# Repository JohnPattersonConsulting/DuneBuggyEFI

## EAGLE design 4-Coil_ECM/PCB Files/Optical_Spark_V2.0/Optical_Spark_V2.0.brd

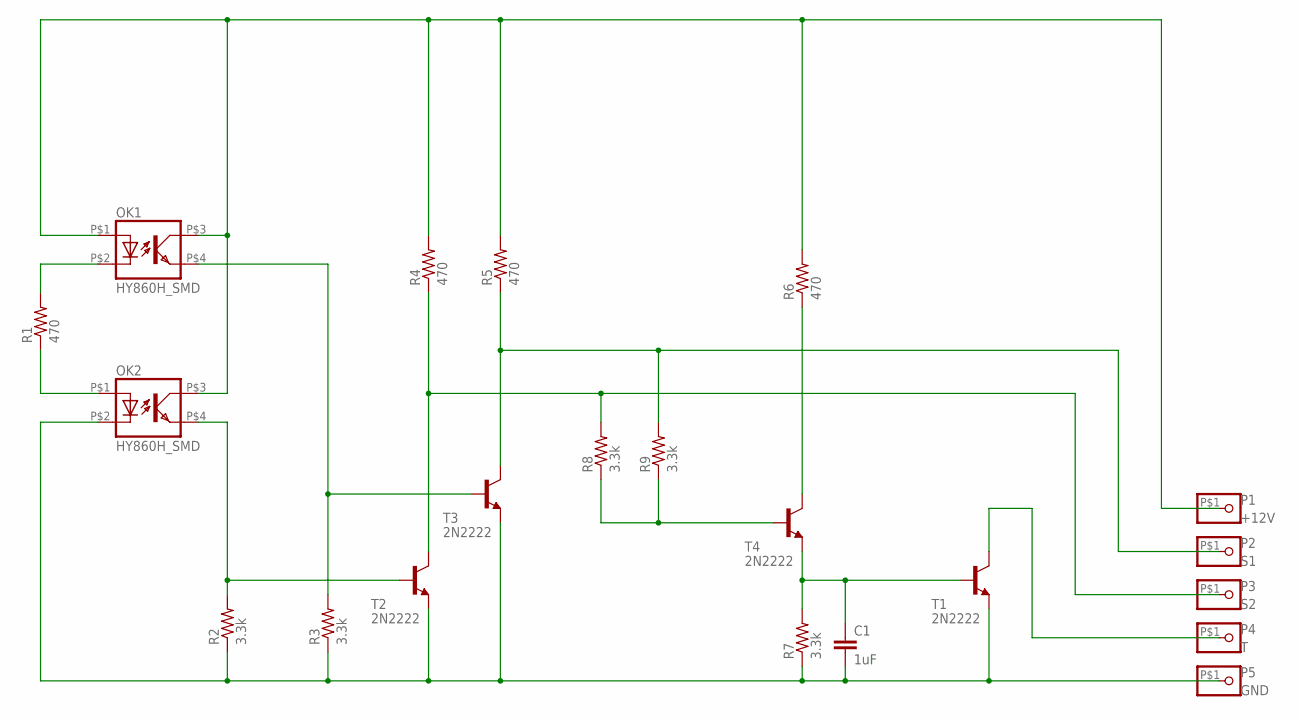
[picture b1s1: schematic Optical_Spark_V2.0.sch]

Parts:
C1: 1uF; SMALLCAP_THT_SMD
OK1, OK2: HY860H_SMD
P1: +12V; PAD
P2: S1; PAD
P3: S2; PAD
P4: T; PAD
P5: GND; PAD
R1, R4, R5, R6: 470; 0.25W_THT_SMD
R2, R3, R7, R8, R9: 3.3k; 0.25W_THT_SMD_SMALL
T1, T2, T3, T4: 2N2222; NPN_THT_SMD_EBC

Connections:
unnamed: OK1.P$2 (C), R1.P$2 (2)
unnamed: OK2.P$1 (A), R1.P$1 (1)
unnamed: C1.P$2 (2), OK2.P$2 (C), P5.P$1, R2.P$1 (1), R3.P$1 (1), R7.P$1 (1), T1.P$1 (E), T2.P$1 (E), T3.P$1 (E)
unnamed: OK1.P$1 (A), OK1.P$3 (COL), OK2.P$3 (COL), P1.P$1, R4.P$2 (2), R5.P$2 (2), R6.P$2 (2)
unnamed: C1.P$1 (1), R7.P$2 (2), T1.P$2 (B), T4.P$1 (E)
unnamed: OK2.P$4 (EMIT), R2.P$2 (2), T2.P$2 (B)
unnamed: OK1.P$4 (EMIT), R3.P$2 (2), T3.P$2 (B)
unnamed: P2.P$1, R5.P$1 (1), R9.P$2 (2), T3.P$3 (C)
unnamed: P3.P$1, R4.P$1 (1), R8.P$2 (2), T2.P$3 (C)
unnamed: R6.P$1 (1), T4.P$3 (C)
unnamed: P4.P$1, T1.P$3 (C)
unnamed: R8.P$1 (1), R9.P$1 (1), T4.P$2 (B)

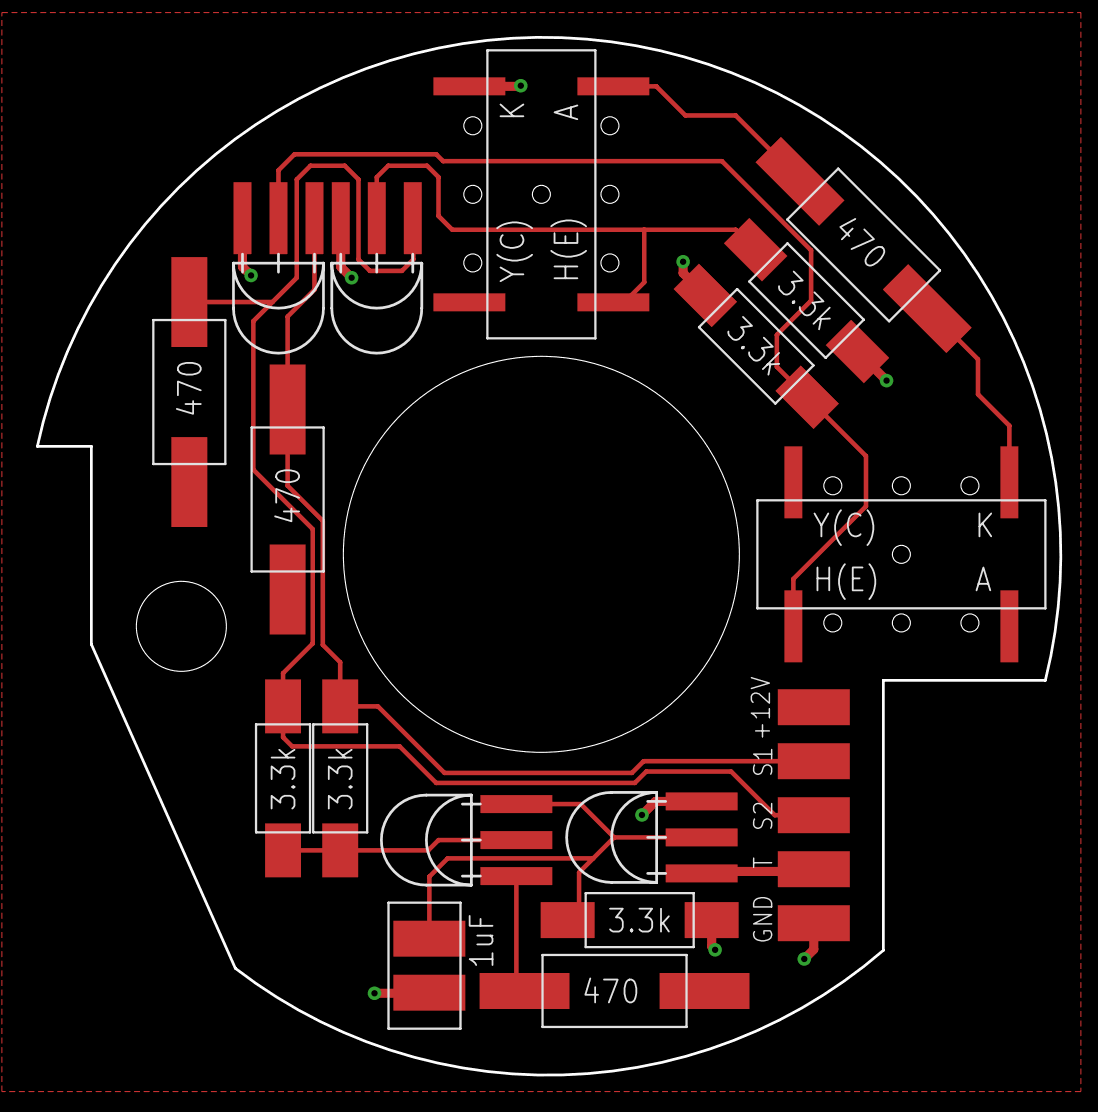
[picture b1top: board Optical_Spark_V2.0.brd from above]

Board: 2 copper layers, 56.9 x 57.6 mm, 21 parts (0 on the bottom side), 12 nets.

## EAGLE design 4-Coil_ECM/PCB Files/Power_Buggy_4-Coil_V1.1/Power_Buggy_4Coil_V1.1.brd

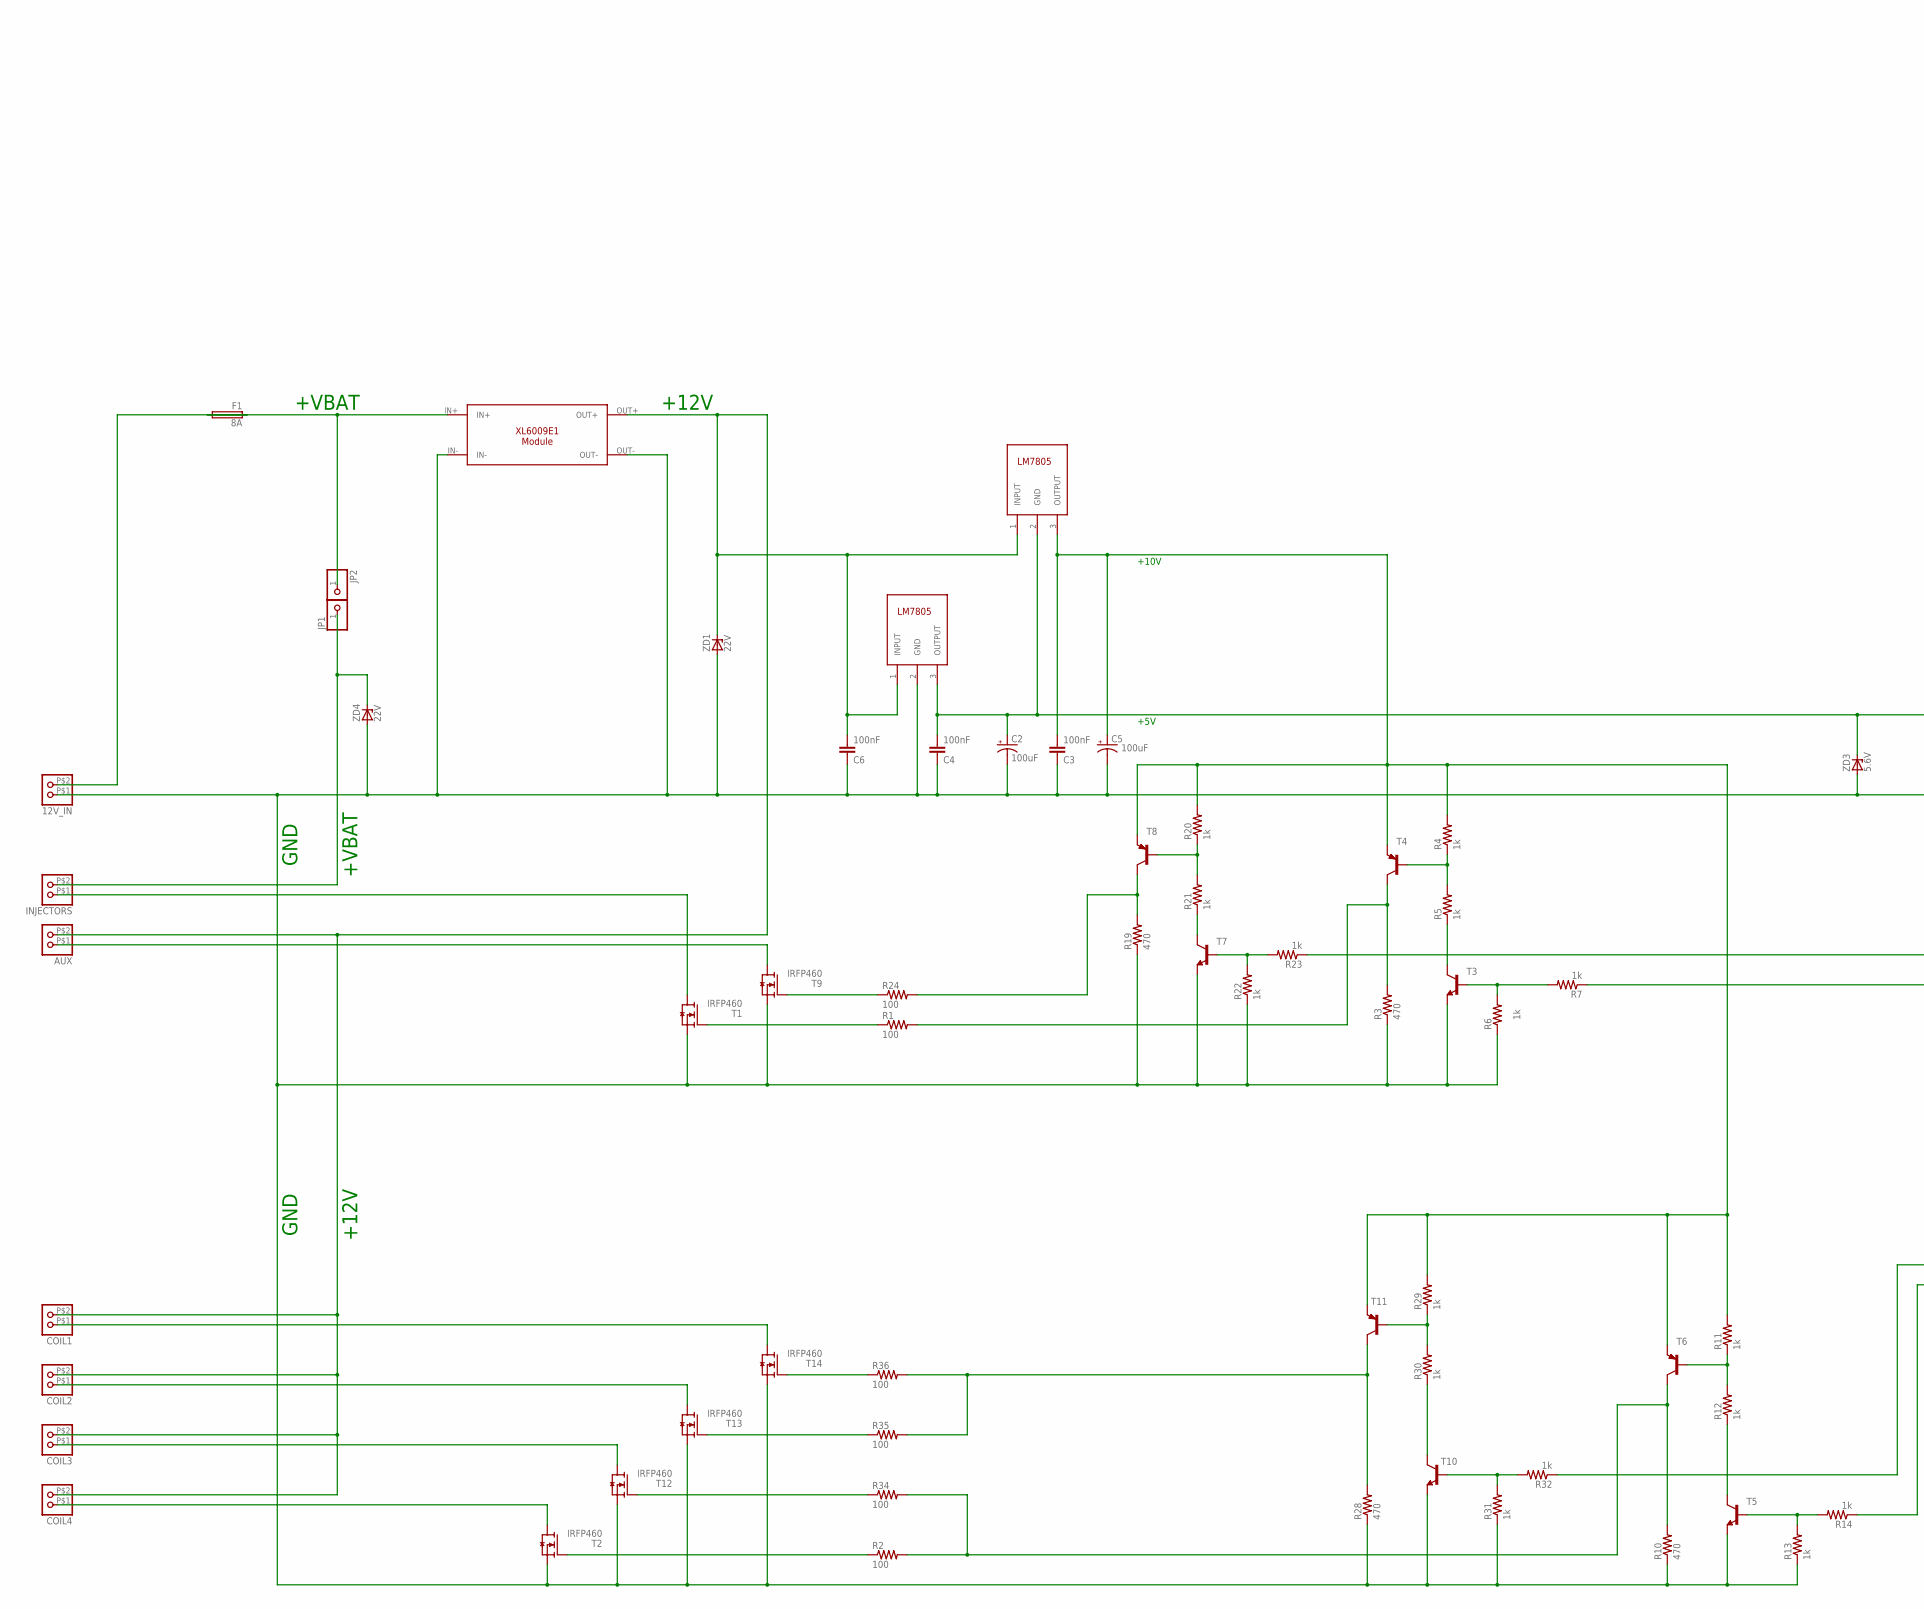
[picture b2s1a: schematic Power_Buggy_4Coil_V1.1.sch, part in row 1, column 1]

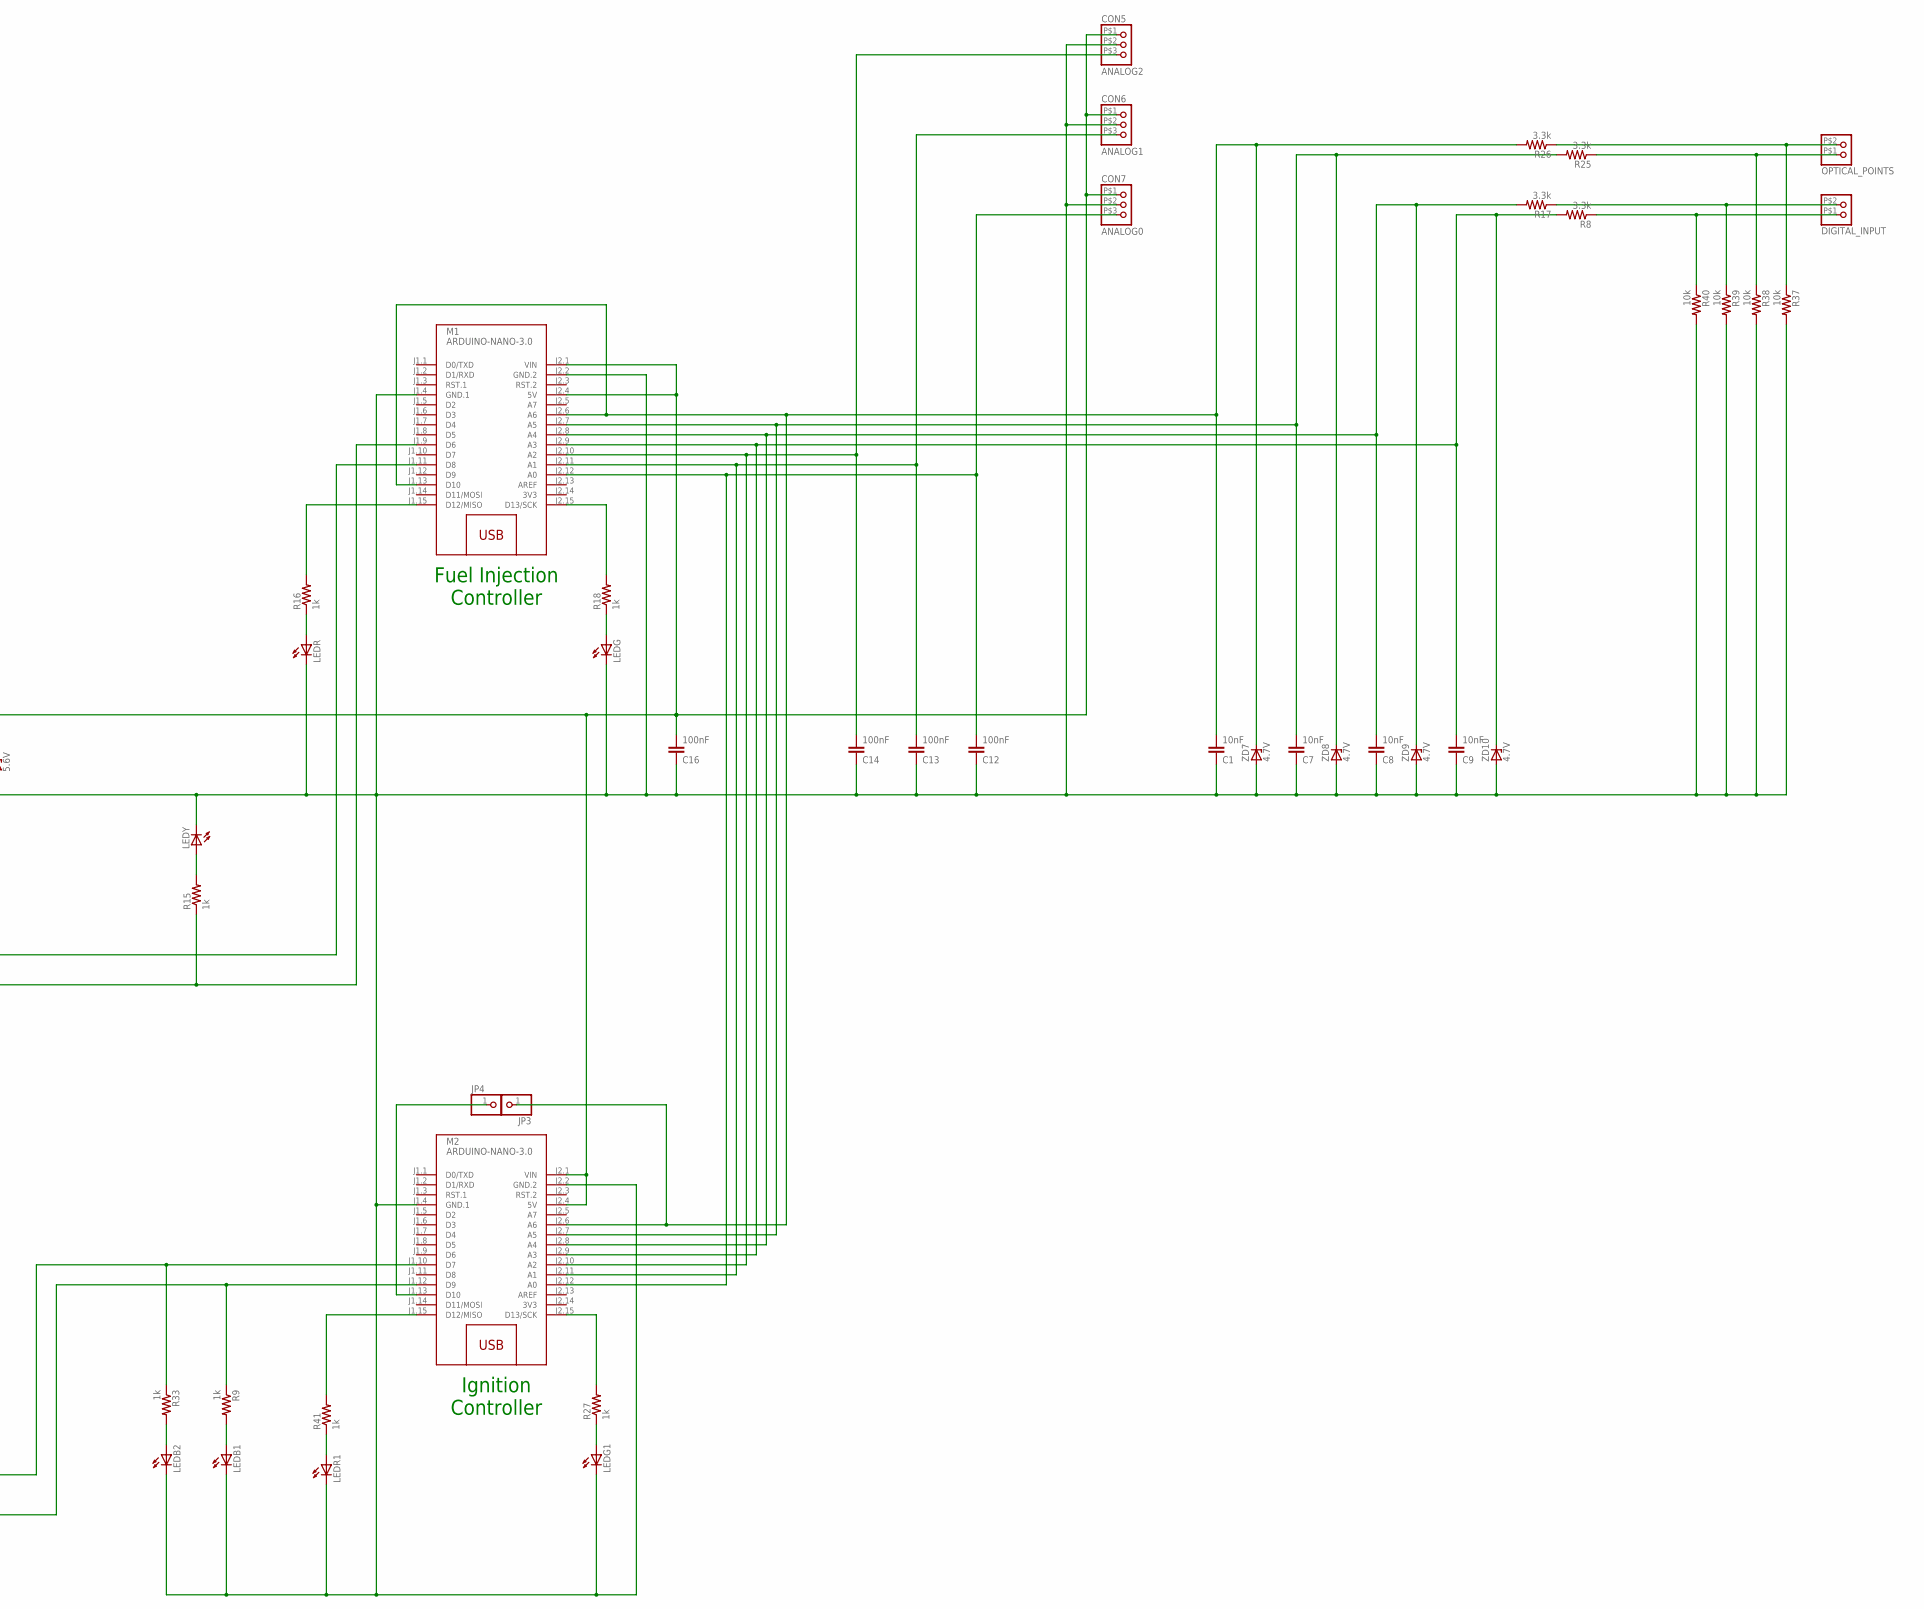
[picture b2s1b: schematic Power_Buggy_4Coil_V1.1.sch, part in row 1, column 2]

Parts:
12V_IN: EBBA-02-C-SS-BU
AUX: EBBA-02-C-SS-BU
C1, C7, C8, C9: 10nF; C050-025X075
C2, C5: 100uF; E2-5
C3, C4, C6, C12, C13, C14, C16: 100nF; C050-025X075
COIL1, COIL2, COIL3, COIL4: EBBA-02-C-SS-BU
CON5: ANALOG2; 2.0MM_X3
CON6: ANALOG1; 2.0MM_X3
CON7: ANALOG0; 2.0MM_X3
DIGITAL_INPUT: EBBA-02-C-SS-BU
F1: 8A; GSH15
INJECTORS: EBBA-02-C-SS-BU
JP1, JP2, JP3, JP4: PINHD-1X1; 1X01
LEDB1, LEDB2: LED3MM
LEDG, LEDG1: LED3MM
LEDR, LEDR1: LED3MM
LEDY: LED3MM
M1, M2: ARDUINO-NANO-3.0
OPTICAL_POINTS: EBBA-02-C-SS-BU
R1, R2, R24, R34, R35, R36: 100; 0207/10
R3, R10, R19, R28: 470; 0207/10
R4, R5, R6, R7, R9, R11, R12, R13, R14, R15, R16, R18, R20, R21, R22, R23, R27, R29, R30, R31, R32, R33, R41: 1k; 0207/10
R8, R17, R25, R26: 3.3k; 0207/10
R37, R38, R39, R40: 10k; 0207/10
REG1, REG2: LM7805_VERT; TO220_VERT
T1, T2, T9, T12, T13, T14: IRFP460; TO-247_HORIZONTAL
T3, T5, T7, T10: -NPN-TO92-EBC; TO92-EBC
T4, T6, T8, T11: BCX58-PNP-TO92-EBC; TO92-EBC
U$2: XL6009E1_MOD
ZD1, ZD4: 22V; C1702-15
ZD3: 5.6V; C1702-15
ZD7, ZD8, ZD9, ZD10: 4.7V; DO41Z10

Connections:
3V3: M1.J2.14 (3V3), M2.J2.14 (3V3)
unnamed: R19.2, R24.2, T8.C
unnamed: AUX.P$2 (2), C6.2, COIL1.P$2 (2), COIL2.P$2 (2), COIL3.P$2 (2), COIL4.P$2 (2), REG1.1 (INPUT), REG2.1 (INPUT), U$2.OUT+, ZD1.C
unnamed: 12V_IN.P$1 (1), C1.1, C2.-, C3.1, C4.1, C5.-, C6.1, C7.1, C8.1, C9.1, C12.1, C13.1, C14.1, C16.1, CON5.P$2 (2), CON6.P$2 (2), CON7.P$2 (2), LEDB1.K (C), LEDB2.K (C), LEDG.K (C), LEDG1.K (C), LEDR.K (C), LEDR1.K (C), LEDY.K (C), M1.J1.4 (GND.1), M1.J2.2 (GND.2), M2.J1.4 (GND.1), M2.J2.2 (GND.2), R3.1, R6.1, R10.1, R13.1, R19.1, R22.1, R28.1, R31.1, R37.2, R38.2, R39.2, R40.2, REG1.2 (GND), T1.S, T2.S, T3.E, T5.E, T7.E, T9.S, T10.E, T12.S, T13.S, T14.S, U$2.IN-, U$2.OUT-, ZD1.A, ZD3.A, ZD4.A, ZD7.A, ZD8.A, ZD9.A, ZD10.A
unnamed: C2.+, C4.2, C16.2, CON5.P$1 (1), CON6.P$1 (1), CON7.P$1 (1), M1.J2.1 (VIN), M1.J2.4 (5V), M2.J2.1 (VIN), M2.J2.4 (5V), REG1.3 (OUTPUT), REG2.2 (GND), ZD3.C
unnamed: INJECTORS.P$1 (1), T1.D
unnamed: C3.2, C5.+, R4.2, R11.2, R20.2, R29.2, REG2.3 (OUTPUT), T4.E, T6.E, T8.E, T11.E
unnamed: R28.2, R35.2, R36.2, T11.C
unnamed: R2.1, T2.G
unnamed: R1.1, T1.G
unnamed: R1.2, R3.2, T4.C
unnamed: R5.1, T3.C
unnamed: R6.2, R7.2, T3.B
unnamed: R4.1, R5.2, T4.B
unnamed: M1.J1.9 (D6), R7.1, R15.1
unnamed: R20.1, R21.2, T8.B
unnamed: R29.1, R30.2, T11.B
unnamed: INJECTORS.P$2 (2), JP1.1, ZD4.C
unnamed: F1.2, JP2.1, U$2.IN+
unnamed: R2.2, R10.2, R34.2, T6.C
unnamed: M1.J1.15 (D12/MISO), R16.2
unnamed: R11.1, R12.2, T6.B
unnamed: 12V_IN.P$2 (2), F1.1
unnamed: R12.1, T5.C
unnamed: LEDR.A, R16.1
unnamed: M1.J2.15 (D13/SCK), R18.2
unnamed: LEDG.A, R18.1
unnamed: C9.2, M1.J2.9 (A3), M2.J2.9 (A3), R8.2, ZD10.C
unnamed: OPTICAL_POINTS.P$1 (1), R25.1, R38.1
unnamed: LEDY.A, R15.2
unnamed: LEDB1.A, R9.2
unnamed: R21.1, T7.C
unnamed: R22.2, R23.2, T7.B
unnamed: C12.2, CON7.P$3 (3), M1.J2.12 (A0), M2.J2.12 (A0)
unnamed: R13.2, R14.2, T5.B
unnamed: M1.J1.11 (D8), R23.1
unnamed: C13.2, CON6.P$3 (3), M1.J2.11 (A1), M2.J2.11 (A1)
unnamed: R24.1, T9.G
unnamed: AUX.P$1 (1), T9.D
unnamed: C8.2, M1.J2.8 (A4), M2.J2.8 (A4), R17.2, ZD9.C
unnamed: C7.2, M1.J2.7 (A5), M2.J2.7 (A5), R25.2, ZD8.C
unnamed: C1.2, JP3.1, M1.J1.13 (D10), M1.J2.6 (A6), M2.J2.6 (A6), R26.2, ZD7.C
unnamed: OPTICAL_POINTS.P$2 (2), R26.1, R37.1
unnamed: DIGITAL_INPUT.P$1 (1), R8.1, R40.1
unnamed: DIGITAL_INPUT.P$2 (2), R17.1, R39.1
unnamed: M2.J2.15 (D13/SCK), R27.2
unnamed: LEDG1.A, R27.1
unnamed: R30.1, T10.C
unnamed: R31.2, R32.2, T10.B
unnamed: C14.2, CON5.P$3 (3), M1.J2.10 (A2), M2.J2.10 (A2)
unnamed: M2.J1.10 (D7), R32.1, R33.1
unnamed: LEDB2.A, R33.2
unnamed: M2.J1.12 (D9), R9.1, R14.1
unnamed: R34.1, T12.G
unnamed: R35.1, T13.G
unnamed: R36.1, T14.G
unnamed: COIL4.P$1 (1), T2.D
unnamed: COIL3.P$1 (1), T12.D
unnamed: COIL2.P$1 (1), T13.D
unnamed: COIL1.P$1 (1), T14.D
unnamed: M2.J1.15 (D12/MISO), R41.2
unnamed: LEDR1.A, R41.1
unnamed: JP4.1, M2.J1.13 (D10)

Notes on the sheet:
+10V
+5V
Fuel Injection Controller
Ignition Controller
+12V
GND
+VBAT

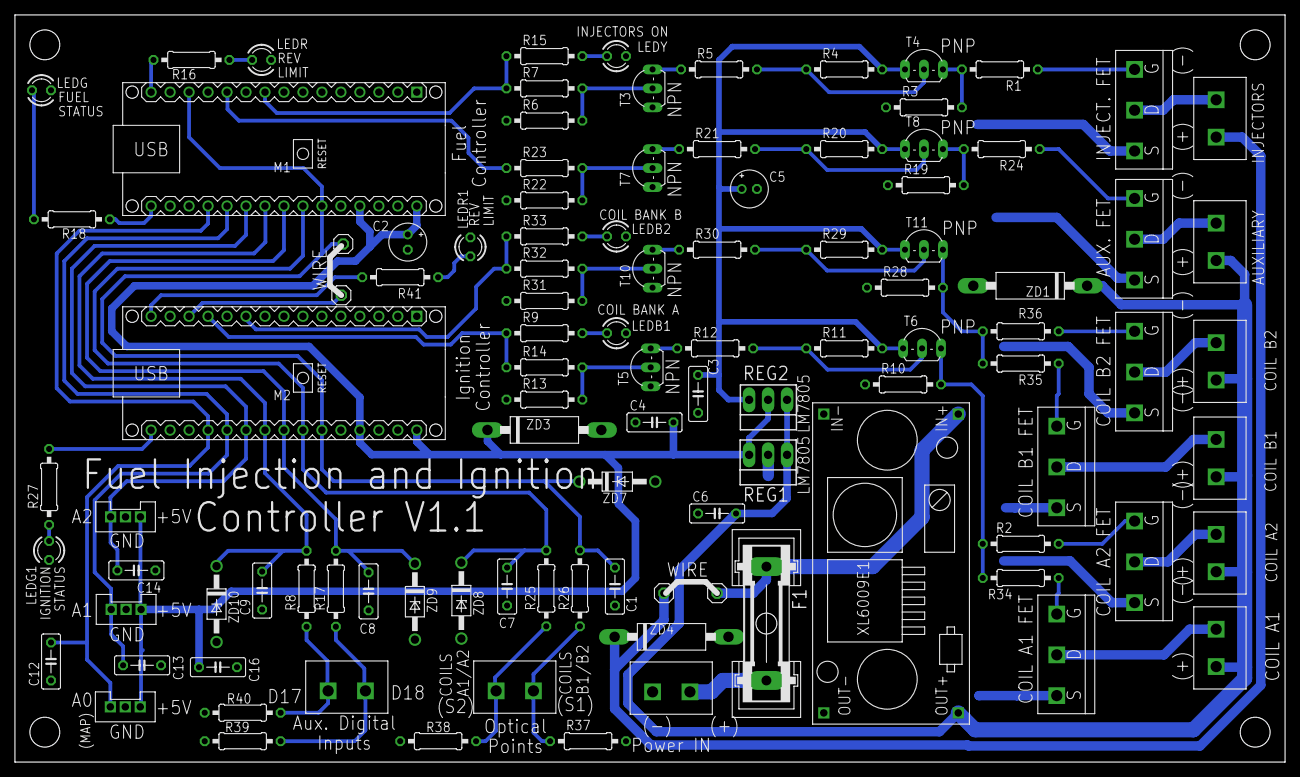
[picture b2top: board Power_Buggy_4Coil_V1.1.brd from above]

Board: 1 copper layer, 170.0 x 100.0 mm, 104 parts (0 on the bottom side), 63 nets.

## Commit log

2020-12-21 Uploaded 2-sensor EFI files V1.0
    Uploaded 2-sensor EFI files V1.0 including Arduino program and hand-sketched schematic of hardware.
2021-03-06 Added MAP_EFI V2, which includes AFR table and RoCoMAP
2021-03-22 Create LICENSE
2021-05-13 Updated MAP_EFI_V2 to MAP_EFI_V2.1
    Fixed reversed order of parameters in call to AFR(), as kindly pointed out by Dany Ravikovitch on YouTube. Thank you!
2022-02-10 Added new files for EFI+Ignition PCB and control code.
2022-02-11 Updated injector update interval to 30ms for better fuel mixture homogeneity. Revert to 50000 if your injectors have problems at low duty cycle..
2022-02-11 Added a picture of the PCB for reference.
2022-03-13 Updated BOM to include mechanical parts.
2022-03-13 Updated silkscreen on PCB Gerber files.
2022-03-17 Removed unnecessary inductor in BOM
2022-05-30 Added files for new 4-coil ECM system.
2022-06-12 Contributed optical rotor CAD files
2022-07-23 Added distributor cover cap CAD files.
2023-04-02 Added a 555-based gate driver design by soupflood.

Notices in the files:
parts and their libraries:
diy-modules: Released under the Creative Commons Attribution 4.0 International License: http://creativecommons.org/licenses/by/4.0
